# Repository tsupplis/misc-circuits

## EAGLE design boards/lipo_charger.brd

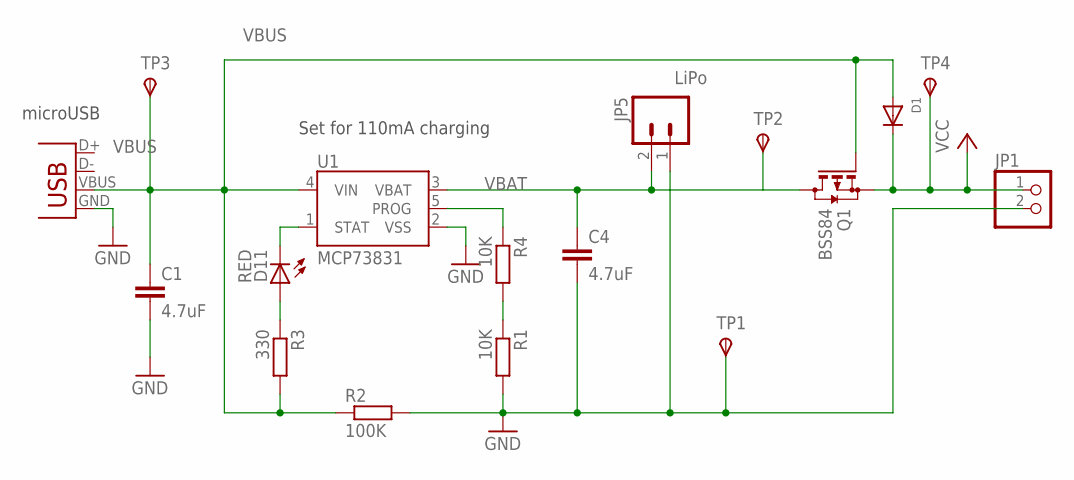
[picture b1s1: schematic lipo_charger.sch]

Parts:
C1, C4: 4.7uF; C0805
D1: DIODESOD-123; SOD-123
D11: RED; LED-1206
JP1: PINHD-1X2; 1X02
JP5: LiPo; JST-2-PTH
Q1: BSS84; SOT23
R1, R4: 10K; R0805
R2: 100K; R0805
R3: 330; R0805
TP1, TP2, TP3, TP4: TPSTP09R; TP09R
U1: MCP73831; SOT23-5
X1: Mini USB B; USB-MINIB-OLD

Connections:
unnamed: D11.A, R3.1
PROG: R4.1, U1.5 (PROG)
PROGA: R1.1, R4.2
STAT: D11.C, U1.1 (STAT)
VBAT: C4.1, JP5.2, Q1.3 (D), TP2.TP, U1.3 (VBAT)
VBUS: C1.1, D1.A, Q1.1 (G), R2.1, R3.2, TP3.TP, U1.4 (VIN), X1.VBUS
VCC: D1.C, JP1.1, Q1.2 (S), TP4.TP
VSS: C1.2, C4.2, JP1.2, JP5.1, R1.2, R2.2, TP1.TP, U1.2 (VSS), X1.GND

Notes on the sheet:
Set for 110mA charging
microUSB

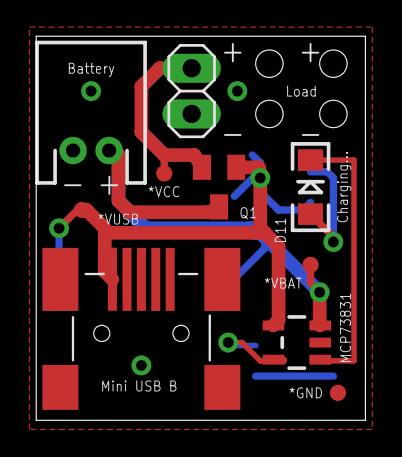
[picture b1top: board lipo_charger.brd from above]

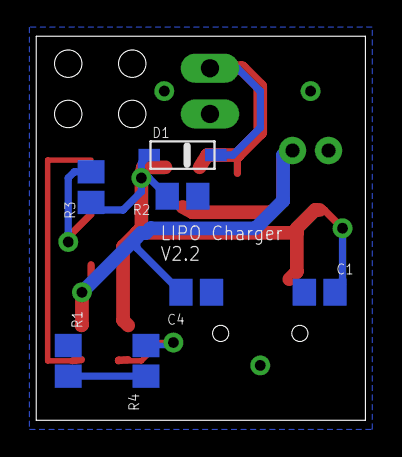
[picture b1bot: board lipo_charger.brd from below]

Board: 2 copper layers, 18.3 x 21.3 mm, 17 parts (7 on the bottom side), 8 nets.

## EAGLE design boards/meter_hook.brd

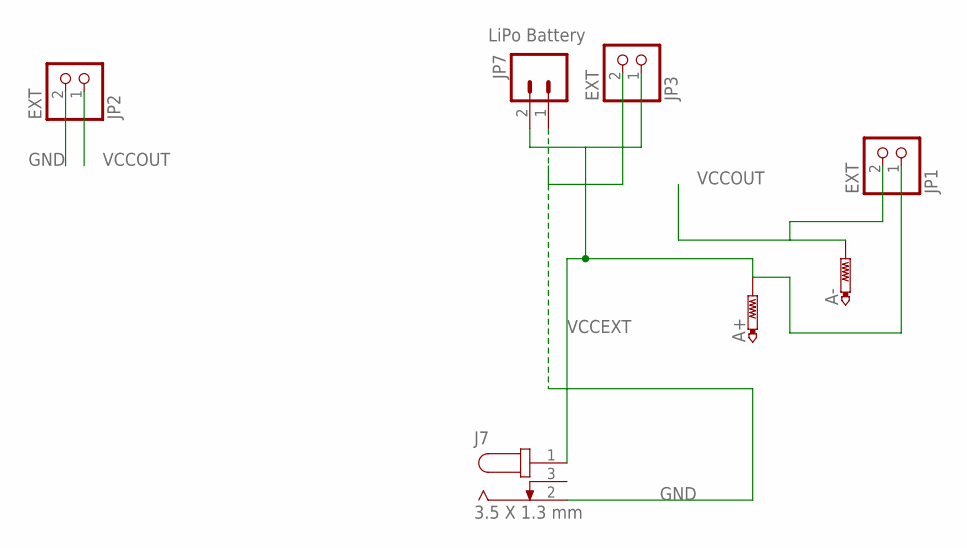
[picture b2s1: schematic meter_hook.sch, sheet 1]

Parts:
A+: PTR1PAD1-13Y; P1-13Y
A-: PTR1PAD1-13Y; P1-13Y
J7: 3.5 X 1.3 mm; 3.5X1.3MM_DC_JACK
JP1, JP2, JP3: EXT; 1X02
JP7: LiPo Battery; JST-2-PTH

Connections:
GND: J7.2, JP2.2, JP3.2, JP7.1
VCCEXT: A+.TP, J7.1, JP1.1, JP3.1, JP7.2
VCCOUT: A-.TP, JP1.2, JP2.1

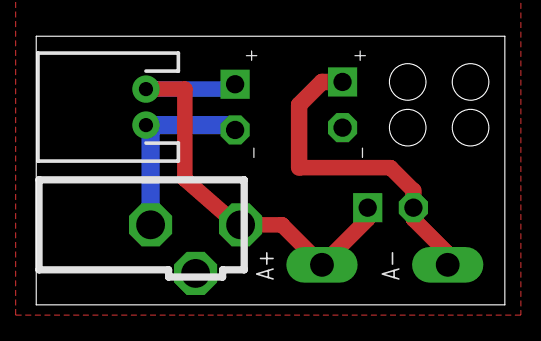
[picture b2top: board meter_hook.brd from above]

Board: 2 copper layers, 26.0 x 14.9 mm, 7 parts (0 on the bottom side), 3 nets.

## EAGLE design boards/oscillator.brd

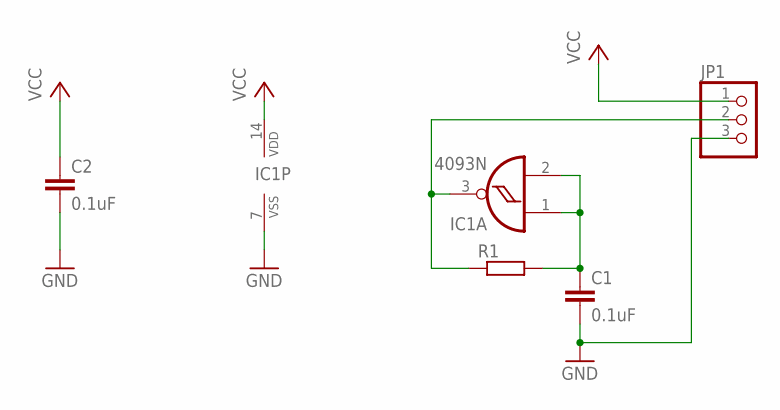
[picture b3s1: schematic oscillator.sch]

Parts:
C1: 0.1uF; C025_050-025X075
C2: 0.1uF; C025-025X050
IC1: 4093N; DIL14
JP1: PINHD-1X3; 1X03
R1: 68K; 0204/7

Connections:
GND: C1.2, C2.2, IC1.7 (VSS), JP1.3
unnamed: IC1.3 (O), JP1.2, R1.1
unnamed: C1.1, IC1.1 (I0), IC1.2 (I1), R1.2
VCC: C2.1, IC1.14 (VDD), JP1.1

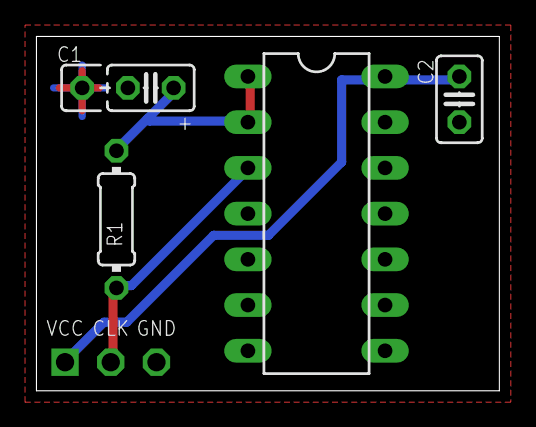
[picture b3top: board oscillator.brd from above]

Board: 2 copper layers, 25.7 x 19.7 mm, 5 parts (0 on the bottom side), 4 nets.

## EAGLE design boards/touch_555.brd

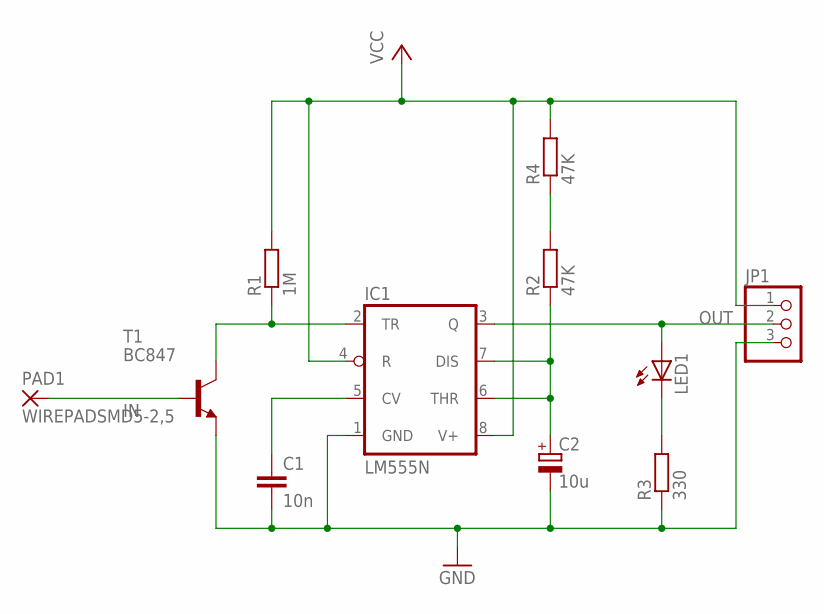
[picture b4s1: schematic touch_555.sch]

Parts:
C1: 10n; C0805
C2: 10u; E2,5-6
IC1: LM555N; DIL08
JP1: PINHD-1X3; 1X03
LED1: LEDCHIPLED_1206; CHIPLED_1206
PAD1: WIREPADSMD5-2,5; 5-2,5
R1: 1M; R0805
R2, R4: 47K; R0805
R3: 330; R0805
T1: BC847; SOT23

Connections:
GND: C1.2, C2.-, IC1.1 (GND), JP1.3, R3.1, T1.2 (E)
IN: PAD1.1, T1.1 (B)
unnamed: LED1.C, R3.2
unnamed: R2.2, R4.1
unnamed: C1.1, IC1.5 (CV)
unnamed: IC1.2 (TR), R1.1, T1.3 (C)
unnamed: C2.+, IC1.6 (THR), IC1.7 (DIS), R2.1
OUT: IC1.3 (Q), JP1.2, LED1.A
VCC: IC1.4 (R), IC1.8 (V+), JP1.1, R1.2, R4.2

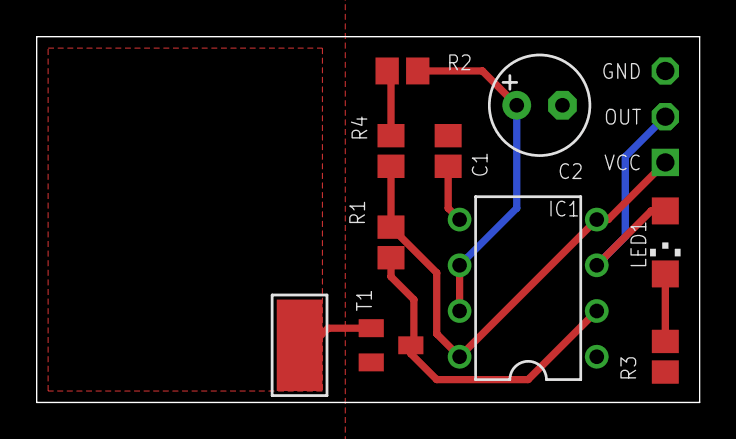
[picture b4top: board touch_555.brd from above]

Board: 2 copper layers, 36.8 x 20.3 mm, 11 parts (0 on the bottom side), 9 nets.

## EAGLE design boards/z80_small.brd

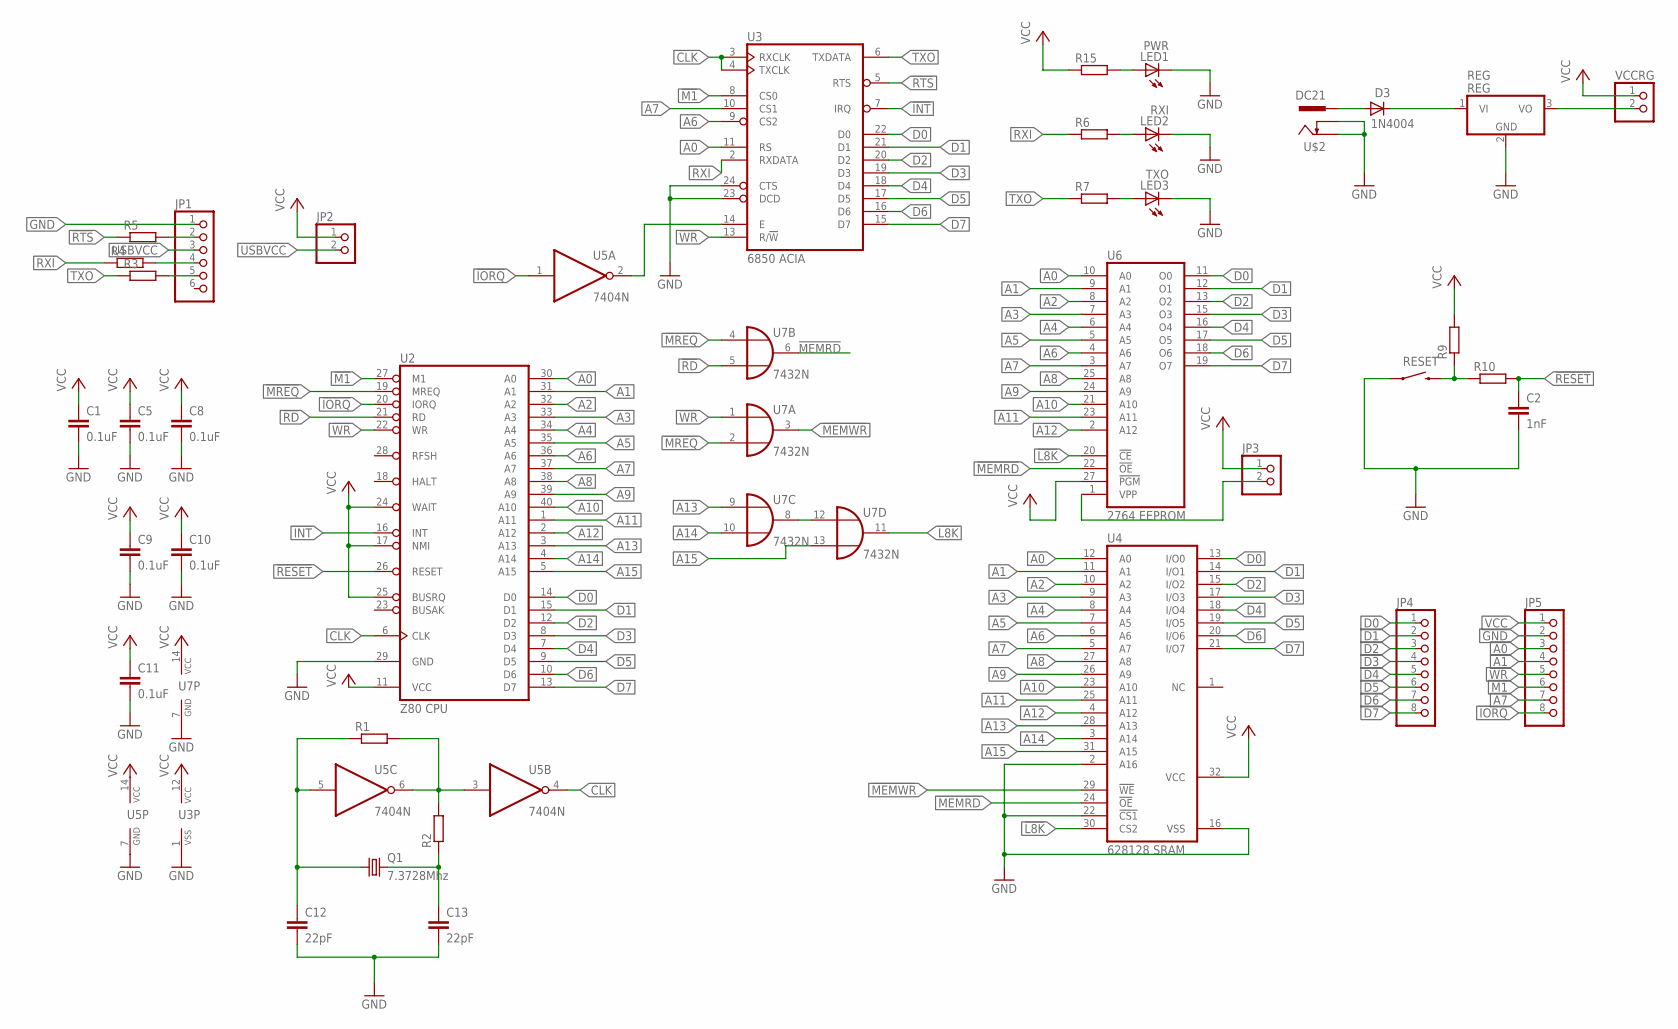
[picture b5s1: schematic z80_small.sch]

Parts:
C1, C5, C8, C9, C10, C11: 0.1uF; C025-025X050
C2: 1nF; C025-025X050
C12, C13: 22pF; C025-025X050
D3: 1N4004; DO41-10
JP1: PINHD-1X6; 1X06
JP2, JP3: PINHD-1X2; 1X02
JP4, JP5: PINHD-1X8; 1X08
LED1: PWR; LED3MM
LED2: RXI; LED3MM
LED3: TXO; LED3MM
Q1: 7.3728Mhz; HC49/S
R1: 1M; 0204/7
R2: 1K; 0204/7
R3, R4, R5: 2K2; 0204/7
R6, R7, R15: 470; 0204/7
R9: 10K; 0204/7
R10: 330; 0204/7
REG: REG; TO220V
RESET: SWITCH-MOMENTARY-2SIDE_EZ; TACTILE-PTH-SIDEEZ
U2: Z80 CPU; DIL40
U3: 6850 ACIA; DIL24
U4: 628128 SRAM; DIL32
U5: 7404N; DIL14
U6: 2764 EEPROM; DIL28
U7: 7432N; DIL14
U$2: DC21; DCSKT
VCCRG: PINHD-1X2; 1X02

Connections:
!INT: U2.16 (INT), U3.7 (IRQ)
!IORQ: JP5.8, U2.20 (IORQ), U5.1 (I)
!L8K: U4.30 (CS2), U6.20 (!CE), U7.11 (O)
!M1: JP5.6, U2.27 (M1), U3.8 (CS0)
!MEMRD: U4.24 (!OE), U6.22 (!OE), U7.6 (O)
!MEMWR: U4.29 (!WE), U7.3 (O)
!MREQ: U2.19 (MREQ), U7.2 (I1), U7.4 (I0)
!PRTS: JP1.2, R5.2
!RD: U2.21 (RD), U7.5 (I1)
!RESET: C2.1, R10.2, U2.26 (RESET)
!RTS: R5.1, U3.5 (RTS)
!WR: JP5.5, U2.22 (WR), U3.13 (R/!W), U7.1 (I0)
+VRAW: D3.C, REG.1 (VI)
A0: JP5.3, U2.30 (A0), U3.11 (RS), U4.12 (A0), U6.10 (A0)
A1: JP5.4, U2.31 (A1), U4.11 (A1), U6.9 (A1)
A2: U2.32 (A2), U4.10 (A2), U6.8 (A2)
A3: U2.33 (A3), U4.9 (A3), U6.7 (A3)
A4: U2.34 (A4), U4.8 (A4), U6.6 (A4)
A5: U2.35 (A5), U4.7 (A5), U6.5 (A5)
A6: U2.36 (A6), U3.9 (CS2), U4.6 (A6), U6.4 (A6)
A7: JP5.7, U2.37 (A7), U3.10 (CS1), U4.5 (A7), U6.3 (A7)
A8: U2.38 (A8), U4.27 (A8), U6.25 (A8)
A9: U2.39 (A9), U4.26 (A9), U6.24 (A9)
A10: U2.40 (A10), U4.23 (A10), U6.21 (A10)
A11: U2.1 (A11), U4.25 (A11), U6.23 (A11)
A12: U2.2 (A12), U4.4 (A12), U6.2 (A12)
A13: U2.3 (A13), U4.28 (A13), U7.9 (I0)
A14: U2.4 (A14), U4.3 (A14), U7.10 (I1)
A15: U2.5 (A15), U4.31 (A15), U7.13 (I1)
CLK: U2.6 (CLK), U3.3 (RXCLK), U3.4 (TXCLK), U5.4 (O)
D0: JP4.1, U2.14 (D0), U3.22 (D0), U4.13 (I/O0), U6.11 (O0)
D1: JP4.2, U2.15 (D1), U3.21 (D1), U4.14 (I/O1), U6.12 (O1)
D2: JP4.3, U2.12 (D2), U3.20 (D2), U4.15 (I/O2), U6.13 (O2)
D3: JP4.4, U2.8 (D3), U3.19 (D3), U4.17 (I/O3), U6.15 (O3)
D4: JP4.5, U2.7 (D4), U3.18 (D4), U4.18 (I/O4), U6.16 (O4)
D5: JP4.6, U2.9 (D5), U3.17 (D5), U4.19 (I/O5), U6.17 (O5)
D6: JP4.7, U2.10 (D6), U3.16 (D6), U4.20 (I/O6), U6.18 (O6)
D7: JP4.8, U2.13 (D7), U3.15 (D7), U4.21 (I/O7), U6.19 (O7)
GND: C1.2, C2.2, C5.2, C8.2, C9.2, C10.2, C11.2, C12.2, C13.2, JP1.1, JP5.2, LED1.K (C), LED2.K (C), LED3.K (C), RESET.1, U2.29 (GND), U3.1 (VSS), U3.23 (DCD), U3.24 (CTS), U4.2 (A16), U4.16 (VSS), U4.22 (!CS1), U5.7 (GND), U6.14 (GND), U7.7 (GND), U$2.2, U$2.3
unnamed: R1.2, R2.2, U5.3 (I), U5.6 (O)
unnamed: U3.14 (E), U5.2 (O)
unnamed: C12.1, Q1.1, R1.1, U5.5 (I)
unnamed: U7.8 (O), U7.12 (I0)
unnamed: C13.1, Q1.2, R2.1
unnamed: REG.3 (VO), VCCRG.2
unnamed: LED2.A, R6.2
unnamed: LED3.A, R7.2
unnamed: D3.A, U$2.1
unnamed: R9.1, R10.1, RESET.2
unnamed: LED1.A, R15.2
PRXI: JP1.4, R4.2
PTXO: JP1.5, R3.2
RXI: R4.1, R6.1, U3.2 (RXDATA)
TXO: R3.1, R7.1, U3.6 (TXDATA)
USBVCC: JP1.3, JP2.2
VCC: C1.1, C5.1, C8.1, C9.1, C10.1, C11.1, JP2.1, JP3.1, JP5.1, R9.2, R15.1, U2.11 (VCC), U2.17 (NMI), U2.24 (WAIT), U2.25 (BUSRQ), U3.12 (VCC), U4.32 (VCC), U5.14 (VCC), U6.27 (!PGM), U6.28 (VCC), U7.14 (VCC), VCCRG.1
VPP: JP3.2, U6.1 (VPP)

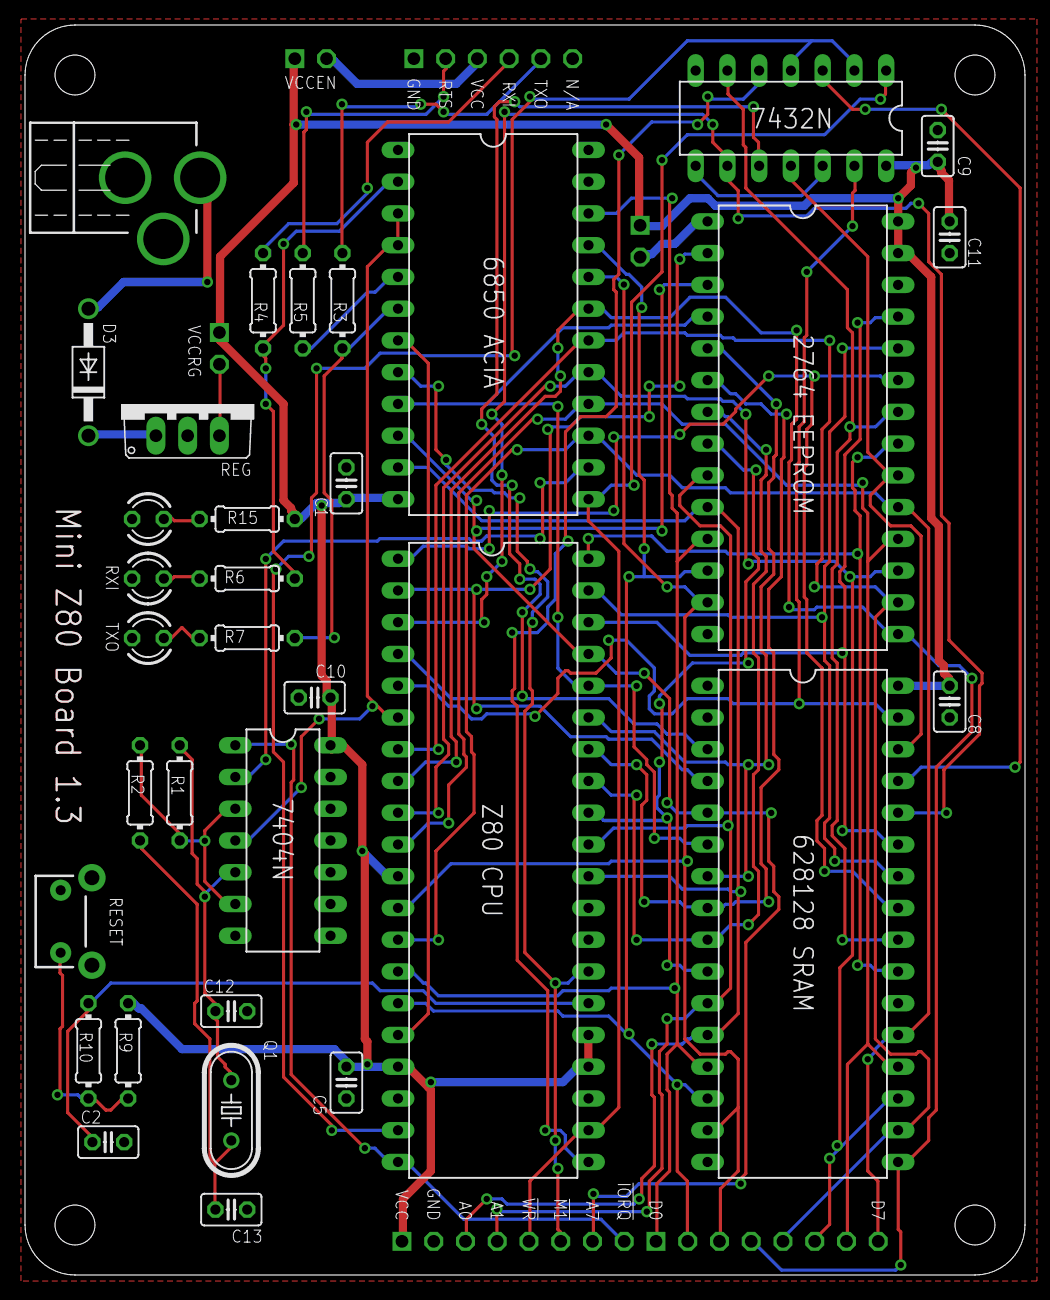
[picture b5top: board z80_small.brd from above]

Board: 2 copper layers, 80.0 x 100.0 mm, 40 parts (0 on the bottom side), 57 nets.

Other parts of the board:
U$1: SMZ80; DP10080_V1

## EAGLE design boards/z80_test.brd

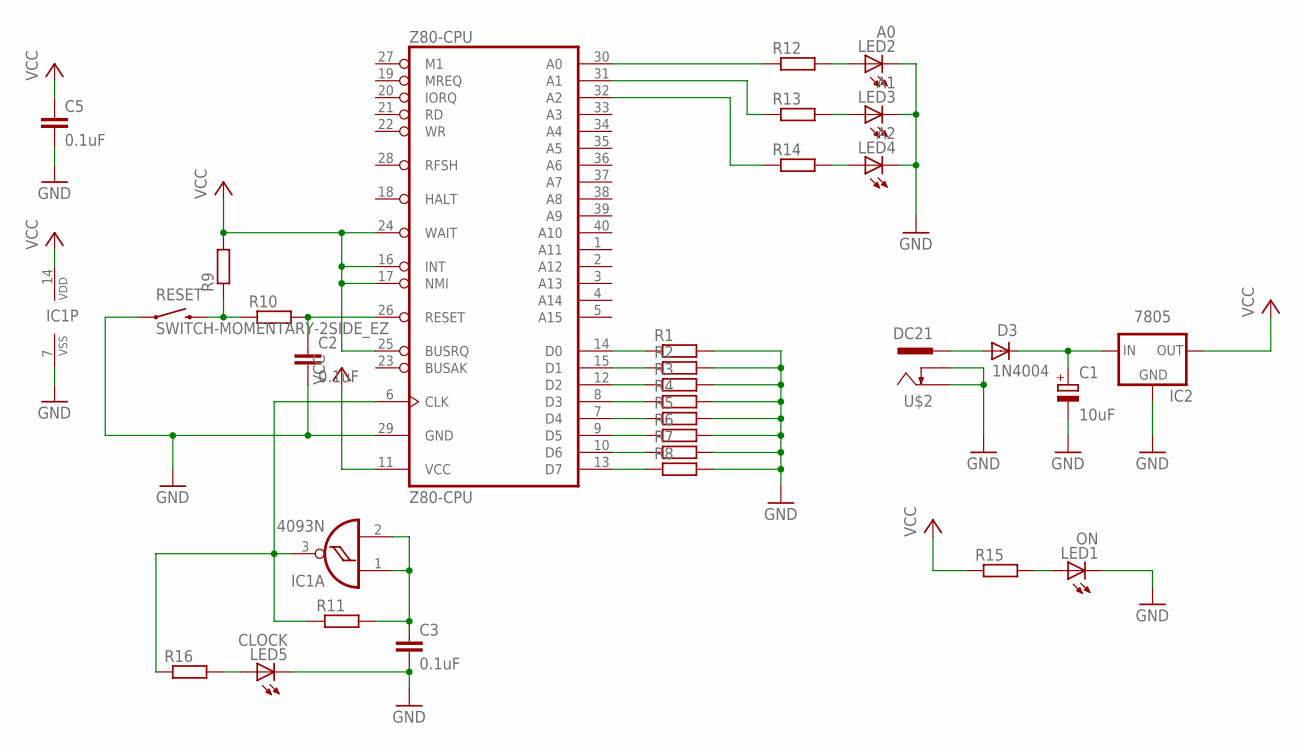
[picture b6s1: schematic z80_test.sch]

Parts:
C1: 10uF; E2,5-6E
C2, C3, C5: 0.1uF; C025-025X050
D3: 1N4004; DO41-10
IC1: 4093N; DIL14
IC2: 7805; 78XXL
LED1: ON; LED3MM
LED2: A0; LED3MM
LED3: A1; LED3MM
LED4: A2; LED3MM
LED5: CLOCK; LED3MM
R1, R2, R3, R4, R5, R6, R7, R8, R9: 10K; 0204/7
R10: 330; 0204/7
R11: 68K; 0204/7
R12, R13, R14, R15, R16: 470; 0204/7
RESET: SWITCH-MOMENTARY-2SIDE_EZ; TACTILE-PTH-SIDEEZ
U$2: DC21; DCSKT
Z80-CPU: Z80-CPU; DIL40

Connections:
+VRAW: C1.+, D3.C, IC2.IN
GND: C1.-, C2.2, C3.2, C5.2, IC1.7 (VSS), IC2.GND, LED1.K (C), LED2.K (C), LED3.K (C), LED4.K (C), LED5.K (C), R1.2, R2.2, R3.2, R4.2, R5.2, R6.2, R7.2, R8.2, RESET.1, U$2.2, U$2.3, Z80-CPU.29 (GND)
unnamed: R12.1, Z80-CPU.30 (A0)
unnamed: R13.1, Z80-CPU.31 (A1)
unnamed: R14.1, Z80-CPU.32 (A2)
unnamed: R1.1, Z80-CPU.14 (D0)
unnamed: R2.1, Z80-CPU.15 (D1)
unnamed: R3.1, Z80-CPU.12 (D2)
unnamed: R4.1, Z80-CPU.8 (D3)
unnamed: R5.1, Z80-CPU.7 (D4)
unnamed: R6.1, Z80-CPU.9 (D5)
unnamed: R7.1, Z80-CPU.10 (D6)
unnamed: R8.1, Z80-CPU.13 (D7)
unnamed: D3.A, U$2.1
unnamed: C2.1, R10.2, Z80-CPU.26 (RESET)
unnamed: R9.1, R10.1, RESET.2
unnamed: IC1.3 (O), R11.1, R16.1, Z80-CPU.6 (CLK)
unnamed: LED2.A, R12.2
unnamed: LED1.A, R15.2
unnamed: LED3.A, R13.2
unnamed: C3.1, IC1.1 (I0), IC1.2 (I1), R11.2
unnamed: LED4.A, R14.2
unnamed: LED5.A, R16.2
VCC: C5.1, IC1.14 (VDD), IC2.OUT, R9.2, R15.1, Z80-CPU.11 (VCC), Z80-CPU.16 (INT), Z80-CPU.17 (NMI), Z80-CPU.24 (WAIT), Z80-CPU.25 (BUSRQ)

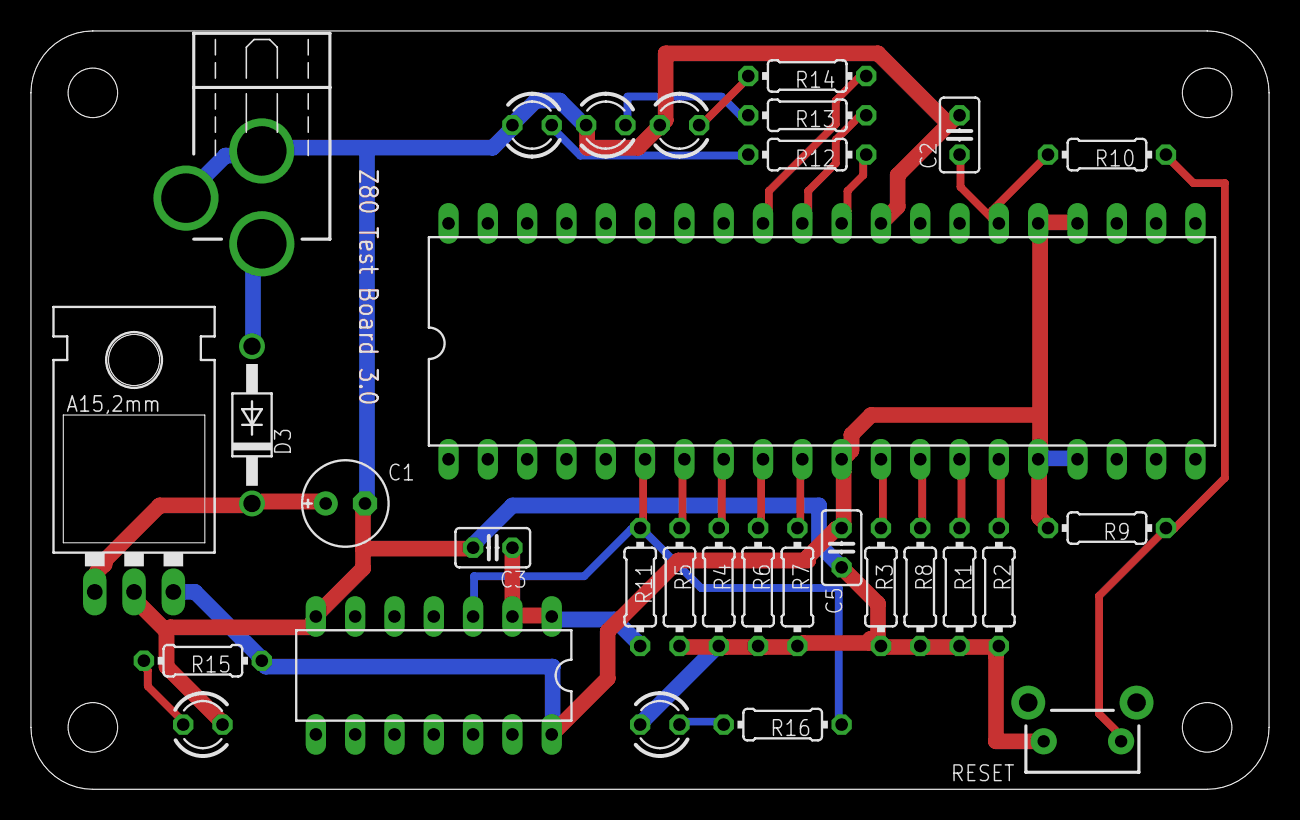
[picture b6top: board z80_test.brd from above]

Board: 2 copper layers, 80.0 x 49.0 mm, 32 parts (0 on the bottom side), 24 nets.

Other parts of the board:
U$1: DP8049_V1

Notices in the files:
parts and their libraries:
SparkFun: Licensing: CC v3.0 Share-Alike You are welcome to use this library for commercial purposes.
